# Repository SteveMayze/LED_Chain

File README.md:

# LED_Chain
An experiment in driving a chain of LEDs

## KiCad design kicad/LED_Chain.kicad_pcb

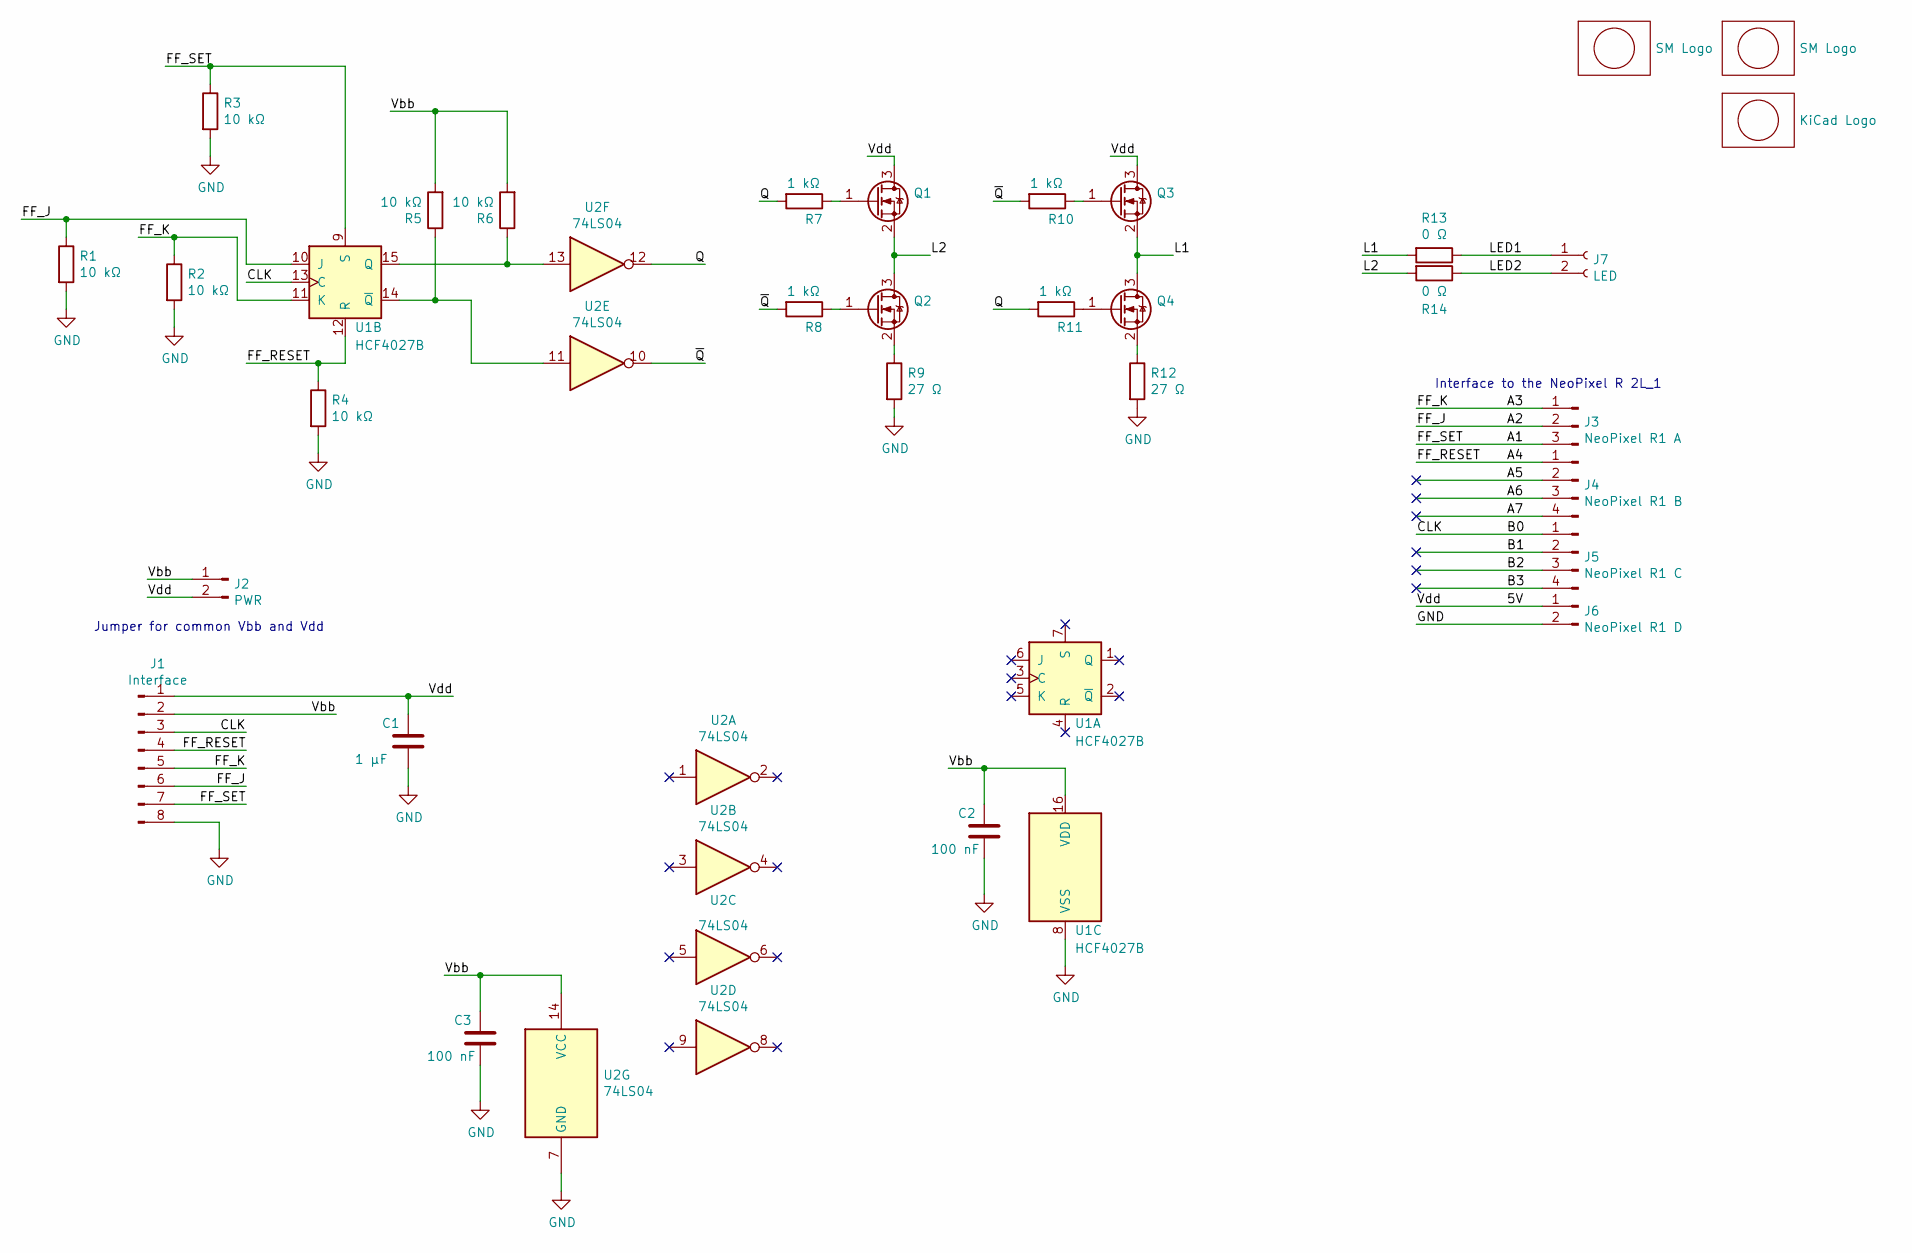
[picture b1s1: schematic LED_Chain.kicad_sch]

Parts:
C1: 1 μF; C_0805_2012Metric
C2, C3: 100 nF; C_0805_2012Metric
J1: Interface; PinHeader_1x08_P2.54mm_Horizontal
J2: PWR; PinHeader_1x02_P2.54mm_Vertical
J3: NeoPixel R1 A; PinHeader_1x03_P2.54mm_Vertical
J4: NeoPixel R1 B; PinHeader_1x04_P2.54mm_Vertical
J5: NeoPixel R1 C; PinHeader_1x04_P2.54mm_Vertical
J6: NeoPixel R1 D; PinHeader_1x02_P2.54mm_Vertical
J7: LED; TerminalBlock_bornier-2_P5.08mm
Lg1, Lg3: SM Logo; MyBasic_rounded_50_1
Lg2: KiCad Logo; KiCad-Logo2_5mm_SilkScreen
Q1, Q2, Q3, Q4: IRLML2502; SOT-23
R1, R2, R3, R4, R5, R6: 10 kΩ; R_0805_2012Metric
R7, R8, R10, R11: 1 kΩ; R_0805_2012Metric
R9, R12: 27 Ω; R_0805_2012Metric
R13, R14: 0 Ω; R_0805_2012Metric
U1: HCF4027B; SO-16-N
U2: 74LS04; SOIC-14

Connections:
/5V: C1.1, J1.1, J2.2, J6.1, Q1.3 (D), Q3.3 (D)
/A1: J1.7, J3.3, R3.1, U1.9 (S)
/A2: J1.6, J3.2, R1.1, U1.10 (J)
/A3: J1.5, J3.1, R2.1, U1.11 (K)
/A4: J1.4, J4.1, R4.1, U1.12 (R)
/A5: J4.2
/A6: J4.3
/A7: J4.4
/B0: J1.3, J5.1, U1.13 (C)
/B1: J5.2
/B2: J5.3
/B3: J5.4
/L1: Q3.2 (S), Q4.3 (D), R13.2
/L2: Q1.2 (S), Q2.3 (D), R14.2
/LED1: J7.1, R13.1
/LED2: J7.2, R14.1
/Q: R7.2, R11.2, U2.12
/Vbb: C2.1, C3.1, J1.2, J2.1, R5.2, R6.2, U1.16 (VDD), U2.14 (VCC)
/~Q: R8.2, R10.2, U2.10
GND: C1.2, C2.2, C3.2, J1.8, J6.2, R1.2, R2.2, R3.2, R4.2, R9.2, R12.2, U1.8 (VSS), U2.7 (GND)
unnamed: Q1.1 (G), R7.1
unnamed: Q2.1 (G), R8.1
unnamed: Q2.2 (S), R9.1
unnamed: Q3.1 (G), R10.1
unnamed: Q4.1 (G), R11.1
unnamed: Q4.2 (S), R12.1
unnamed: R6.1, U1.15 (Q), U2.13
unnamed: R5.1, U1.14 (~Q), U2.11

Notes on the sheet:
Jumper for common Vbb and Vdd
Interface to the NeoPixel R 2L_1

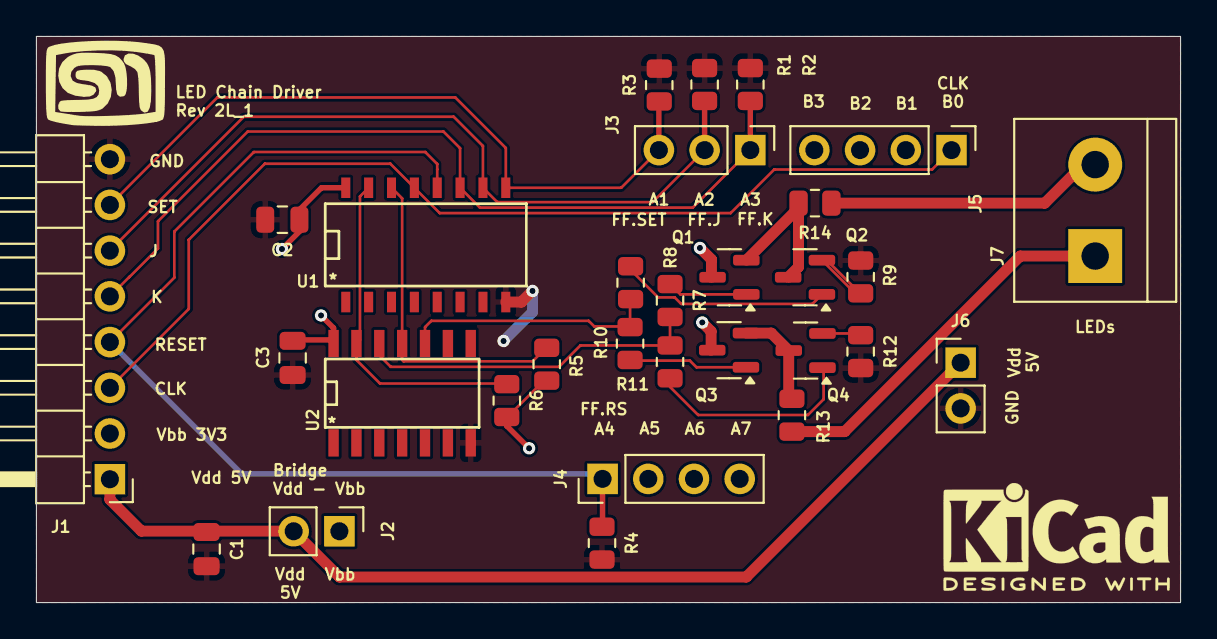
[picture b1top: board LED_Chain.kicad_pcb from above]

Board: 2 copper layers, 63.6 x 31.5 mm, 33 parts (1 on the bottom side), 22 nets.

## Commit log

2020-10-21 Started the schematic
2020-10-24 Schematic and initial layout
2020-10-25 Added a buffer resitor to the gates
2020-10-27 Added some images for the documentation
2020-10-31 Initial configuration for the firmware
2020-11-01 Configuration for 1kHz on pin PB0
2020-11-01 Rudementry clk frequency change to enhance the animation effect
2020-11-02 Improves the period calulation based on frequency
2020-11-02 Makes the frequency selection more flexible and corrects the calculation
2020-11-03 Updated the schematic and started a new layout for the final design
2020-11-05 Adds an implementation for the ATtiny1614
2020-11-08 Another layout attempt - changes to pin layout for Neopixel interface
2020-11-09 Completed the layout
2020-11-09 Completed layout and sent to OSH Park
2020-11-10 Changed the pin allocation to match the PCB changes and some animation timing
2020-12-18 adds the final animation for the gingerbread house
2020-12-19 Some small adjustments to the initialisation
2020-12-21 Makes a small correction to the labelling of the Vbb-Vdd bridge
2020-12-21 Fixes the pin association on J3
2020-12-22 Revert "Fixes the pin association on J3"
    This reverts commit 2cc36517f423e818af2cf15adf9433c164440afc.
2020-12-22 Corrects the pin assignment so that no hardware change is required
    The original pin assignments A1 and A3 have been swapped for simpler layout on the board from what was originally imagined. Rather than making a hardware change, the firmware now has the functions fo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
2021-09-04 Uses a motocontroller as a LED driver and ports the sample from the AT1614
2021-09-05 Adds two more _breathe_ annimations using PWM
2021-09-05 Starting a Fritzing connection
2021-09-07 Adds some results diagrams for the writeup
2021-09-09 Assessing KiCad to Fritzing work steps
2021-10-08 Documentation update
2021-10-09 Adds come media
2024-11-23 Upgraded basic symbols and footprints
2024-11-23 Updated for V8 KiCad
2024-11-23 V8 update
2024-11-24 Started the 12V of the LED Chain
